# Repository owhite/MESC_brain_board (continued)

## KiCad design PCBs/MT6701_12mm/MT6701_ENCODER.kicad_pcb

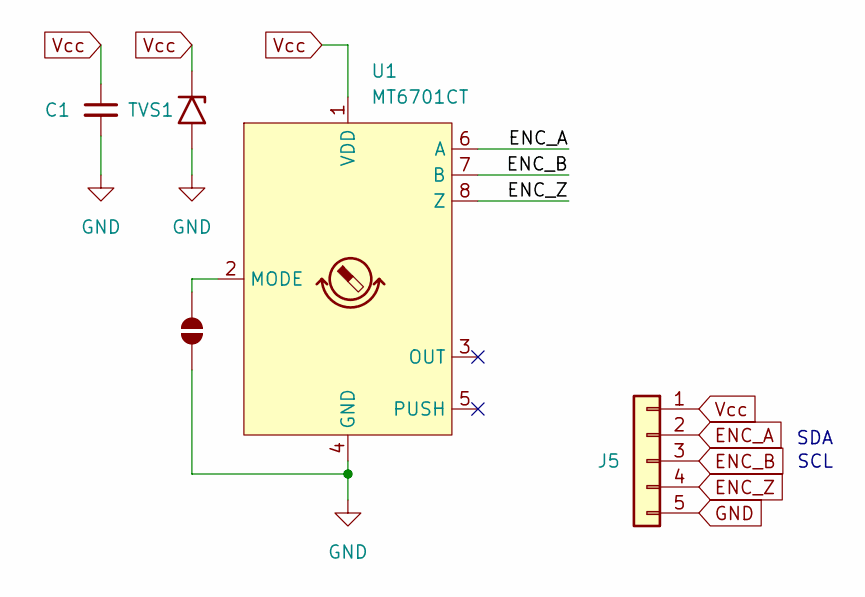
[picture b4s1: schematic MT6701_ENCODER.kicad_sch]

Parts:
C1: C_Small; C_0603_1608Metric
J5: Conn_01x05; PinSocket_1x05_P2.54mm_Vertical
JP1: SolderJumper_2_Open; SolderJumper-2_P1.3mm_Open_RoundedPad1.0x1.5mm
TVS1: SMFJ6.0A / SMFJ6.0CA; C_0805_2012Metric
U1: MT6701CT; SO-8_3.9x4.9mm_P1.27mm

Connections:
ENC_A: J5.2, U1.6 (A)
ENC_B: J5.3, U1.7 (B)
ENC_Z: J5.4, U1.8 (Z)
GND: C1.2, J5.5, JP1.2 (B), TVS1.2 (A2), U1.4 (GND)
unnamed: JP1.1 (A), U1.2 (MODE)
Vcc: C1.1, J5.1, TVS1.1 (A1), U1.1 (VDD)

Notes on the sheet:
SDA
SCL

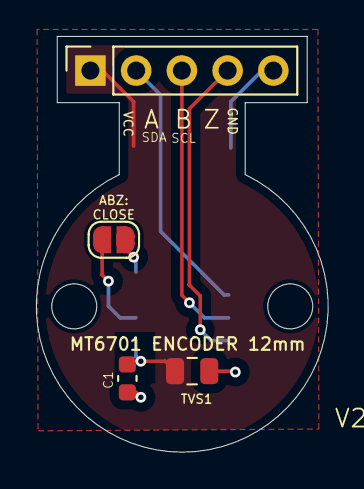
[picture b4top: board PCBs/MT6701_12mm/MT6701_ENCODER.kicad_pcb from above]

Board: 2 copper layers, 16.2 x 23.1 mm, 5 parts (1 on the bottom side), 6 nets.

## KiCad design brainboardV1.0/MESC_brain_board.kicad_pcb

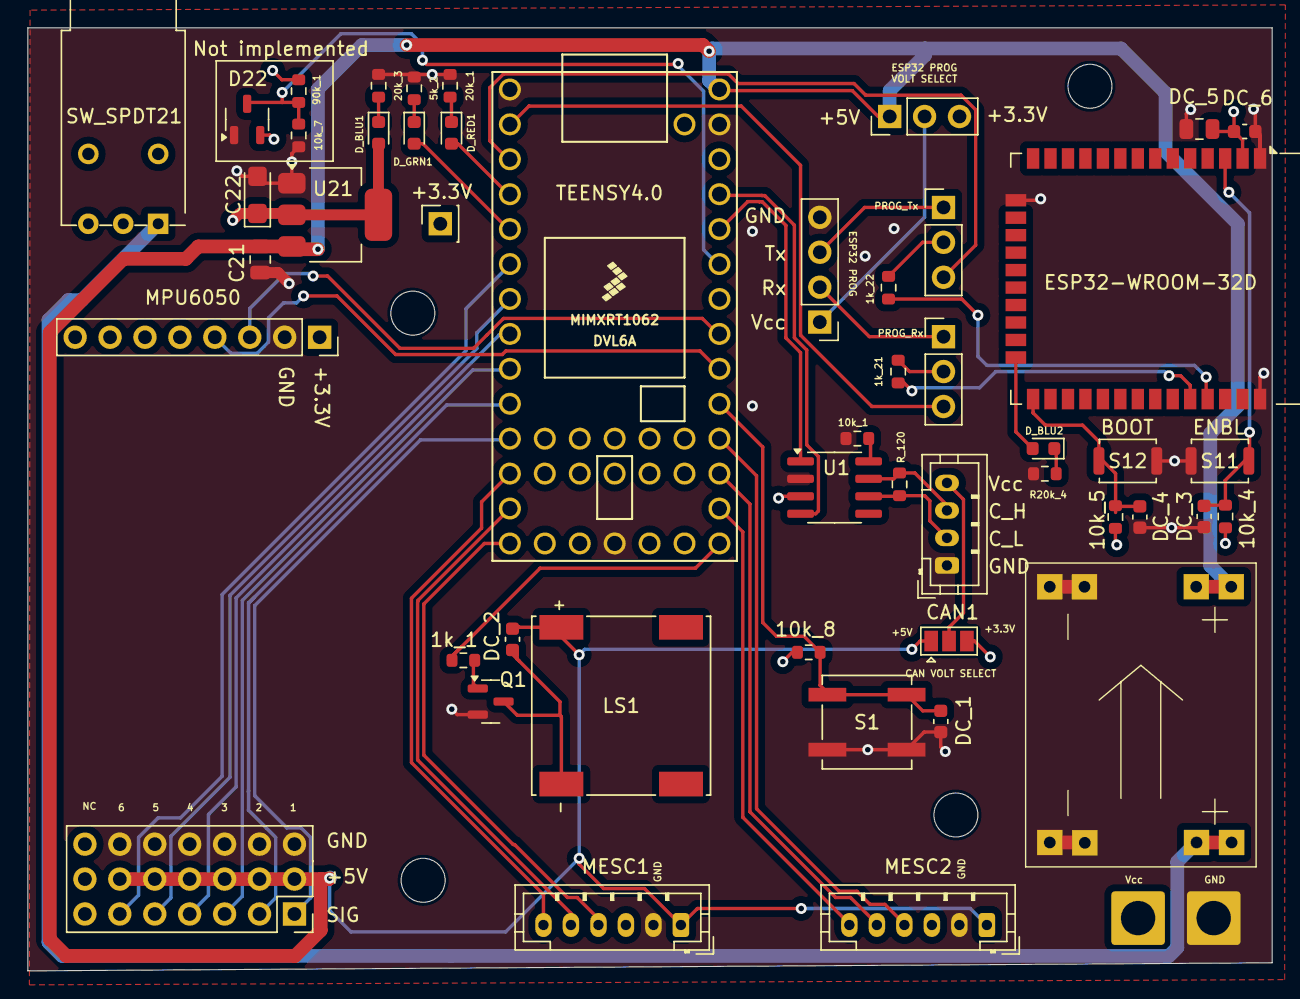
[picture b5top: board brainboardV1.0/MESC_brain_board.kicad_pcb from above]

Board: 4 copper layers, 90.5 x 68.6 mm, 51 parts (0 on the bottom side), 48 nets.

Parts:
1k_1, 10k_1, 10k_4, 10k_5, 10k_7, 10k_8: 10k; R_0603_1608Metric
1k_21, 1k_22: 1k; R_0603_1608Metric
5k_2: 5k; R_0603_1608Metric
20k_1, 20k_3: 20k; R_0603_1608Metric
90k_1: 90k; R_0603_1608Metric
C21: 10uF; C_0805_2012Metric
C22: C_Polarized_Small_US; CP_EIA-3216-18_Kemet-A
CAN1: Conn_01x04; JST_PH_B4B-PH-K_1x04_P2.00mm_Vertical
D22: BAT54S; SOT-23-3
DC_1, DC_2, DC_3, DC_4, DC_6: 100nF; C_0603_1608Metric
DC_5: 10uF; C_0805_2012Metric
D_BLU1: LED BLU; LED_0603_1608Metric
D_BLU2: BLUE; LED_0603_1608Metric
D_GRN1: LED GRN; LED_0603_1608Metric
D_RED1: LED RED; LED_0603_1608Metric
J1: Conn_01x18; my_PinSocket_3x07_P2.54mm_Vertical
J12, J13, J15: Conn_01x03; PinHeader_1x03_P2.54mm_Vertical
J14: SERIAL1; PinHeader_1x04_P2.54mm_Vertical
J22: Conn_01x01; PinSocket_1x01_P2.54mm_Vertical
J24, J25: Conn_01x01; SolderWire-2sqmm_1x01_D2mm_OD3.9mm
JP1: SolderJumper_3_Open; SolderJumper-3_P1.3mm_Open_Pad1.0x1.5mm
LS1: Speaker; SPKR_CDS-13138-SMT-TR
MESC1, MESC2: Conn_01x06; JST_PH_B6B-PH-K_1x06_P2.00mm_Vertical
MP1: Conn_01x08; PinSocket_1x08_P2.54mm_Vertical
Q1: my_BC337; SOT-23
R20k_4: 20k; R_0603_1608Metric
R_120: 120; R_0603_1608Metric
S1: TL3342F160QG; SW_SPST_B3SL-1022P
S11, S12: TL3342F160QG; SW_Push_SPST_NO_Alps_SKRK
SW_SPDT21: SW_SPDT; SW_NKK_BB15AH
U1: TJA1050T/CM,118; SOIC-8_3.9x4.9mm_P1.27mm
U2: Teensy4.0; Teensy40
U11: ESP32-WROOM-32D
U21: LD1117S18TR_SOT223; SOT-223-3_TabPin2
U22: my_buck_boost

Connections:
+3.3V: 10k_4.2, 10k_5.2, 10k_8.2, C22.1, D22.2, DC_5.2, DC_6.1, D_BLU1.2 (A), J15.3, J22.1, JP1.3 (B), MP1.1, U1.3 (VCC), U11.2 (VDD), U21.2 (VO)
+5V: C21.1, DC_2.1, J1.2, J1.5, J1.8, J1.11, J1.14, J1.17, J15.1, JP1.1 (A), LS1.1, MESC1.1, MESC2.1, U2.33 (VIN), U21.3 (VI), U22.7 (Reg_out), U22.8 (Reg_out)
/CAN_RX: U1.4 (R), U2.30 (23_A9_CRX1_MCLK1)
/CAN_TX: U1.1 (D), U2.29 (22_A8_CTX1)
/MPU6050_SCL: MP1.3, U2.26 (19_A5_SCL0)
/MPU6050_SDA: MP1.4, U2.25 (18_A4_SDA0)
BUTTON: 10k_8.1, DC_1.2, S1.2, U2.24 (17_A3_TX4_SDA1)
CAN_HI: CAN1.3, R_120.2, U1.7 (CANH)
CAN_LO: CAN1.2, R_120.1, U1.6 (CANL)
ESP_EN: 10k_4.1, DC_3.2, S11.2, U11.3 (EN)
ESP_RX: J12.3, U2.2 (0_RX1_CRX2_CS1)
ESP_RX_OUT: J12.1, J14.2
ESP_TX: J13.3, U2.3 (1_TX1_CTX2_MISO1)
ESP_TX_OUT: J13.1, J14.3
GND: 5k_2.1, 10k_1.2, 10k_7.2, 20k_1.1, 20k_3.1, C21.2, C22.2, CAN1.1, D22.1, DC_1.1, DC_3.1, DC_4.1, DC_5.1, DC_6.2, J1.3, J1.6, J1.9, J1.12, J1.15, J1.18, J14.4, J24.1, MESC1.2, MESC2.2, MP1.2, Q1.2 (E), R20k_4.1, S1.1, S11.1, S12.1, U1.2 (GND), U2.1 (GND), U2.17 (GND), U2.32 (GND), U11.1 (GND), U11.15 (GND), U11.38 (GND), U21.1 (GND), U22.1 (IN_-), U22.2 (IN_-), U22.5 (Reg_GND), U22.6 (Reg_GND)
IO0: 10k_5.1, DC_4.2, S12.2, U11.25 (IO0)
LED1: D_RED1.2 (A), U2.4 (2_OUT2)
LED2: D_GRN1.2 (A), U2.5 (3_LRCLK2)
unnamed: CAN1.4, JP1.2 (C)
unnamed: 20k_3.2, D_BLU1.1 (K)
unnamed: D_BLU2.2 (A), U11.24 (IO2)
unnamed: D_BLU2.1 (K), R20k_4.2
unnamed: 5k_2.2, D_GRN1.1 (K)
unnamed: 20k_1.2, D_RED1.1 (K)
unnamed: 1k_21.2, J12.2
unnamed: 1k_22.2, J13.2
unnamed: J14.1, J15.2
unnamed: 1k_1.1, Q1.1 (B)
unnamed: DC_2.2, LS1.2, Q1.3 (C)
unnamed: SW_SPDT21.1 (A), U22.3 (IN_+), U22.4 (IN_+)
unnamed: 10k_1.1, U1.8 (Rs)
PB3_1: MESC1.6, U2.12 (10_CS_MQSR)
PB3_2: MESC2.6, U2.21 (14_A0_TX3_SPDIF_OUT)
PB4_1: MESC1.5, U2.13 (11_MOSI_CTX1)
PB4_2: MESC2.5, U2.22 (15_A1_RX3_SPDIF_IN)
PB5_1: MESC1.4, U2.14 (12_MISO_MQSL)
PB5_2: MESC2.4, U2.23 (16_A2_RX4_SCL1)
RC_Mode: J1.7, U2.9 (7_RX2_OUT1A)
RC_Steering: J1.1, U2.11 (9_OUT1C)
RC_Throttle: J1.4, U2.10 (8_TX2_IN1)
RC_X: J1.10, U2.8 (6_OUT1D)
RC_Y: J1.13, U2.7 (5_IN2)
RC_Z: J1.16, U2.6 (4_BCLK2)
SPEAKER: 1k_1.2, U2.20 (13_SCK_CRX1_LED)
U0RXD: 1k_21.1, U11.34 (RXD0/IO3)
U0TXD: 1k_22.1, U11.35 (TXD0/IO1)
VSENSE: 10k_7.1, 90k_1.2, D22.3, U2.28 (21_A7_RX5_BCLK1)
Vcc: J25.1, SW_SPDT21.2 (B)

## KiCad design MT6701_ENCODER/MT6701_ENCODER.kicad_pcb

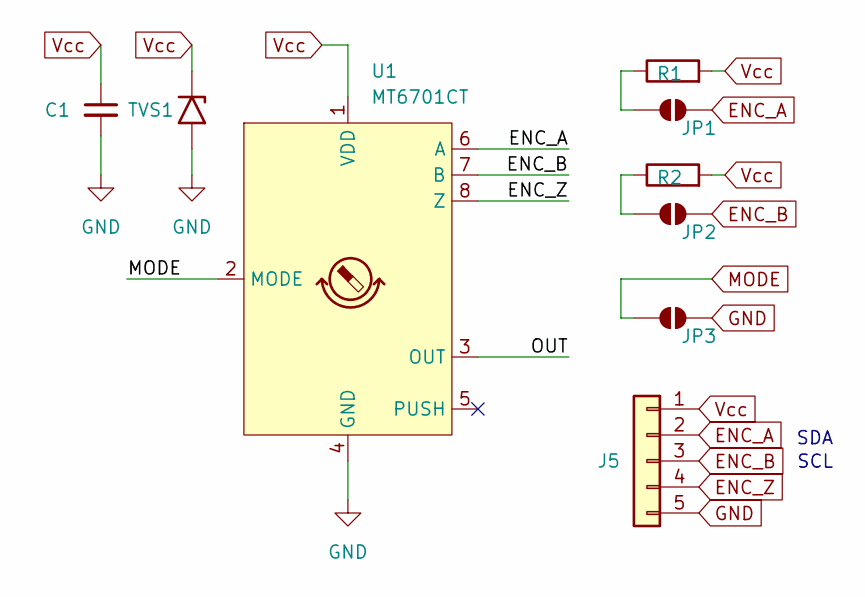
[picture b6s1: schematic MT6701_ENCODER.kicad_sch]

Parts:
C1: C_Small; C_0603_1608Metric
J5: Conn_01x05; PinHeader_1x05_P2.54mm_Vertical
JP1, JP2, JP3: SolderJumper_2_Open; SolderJumper-2_P1.3mm_Open_RoundedPad1.0x1.5mm
R1, R2: R; R_0603_1608Metric
TVS1: SMFJ6.0A / SMFJ6.0CA; C_0805_2012Metric
U1: MT6701CT; SO-8_3.9x4.9mm_P1.27mm

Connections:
/OUT: U1.3 (OUT)
ENC_A: J5.2, JP1.2 (B), U1.6 (A)
ENC_B: J5.3, JP2.2 (B), U1.7 (B)
ENC_Z: J5.4, U1.8 (Z)
GND: C1.2, J5.5, JP3.2 (B), TVS1.2 (A2), U1.4 (GND)
MODE: JP3.1 (A), U1.2 (MODE)
unnamed: JP1.1 (A), R1.1
unnamed: JP2.1 (A), R2.1
Vcc: C1.1, J5.1, R1.2, R2.2, TVS1.1 (A1), U1.1 (VDD)

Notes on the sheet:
SDA
SCL

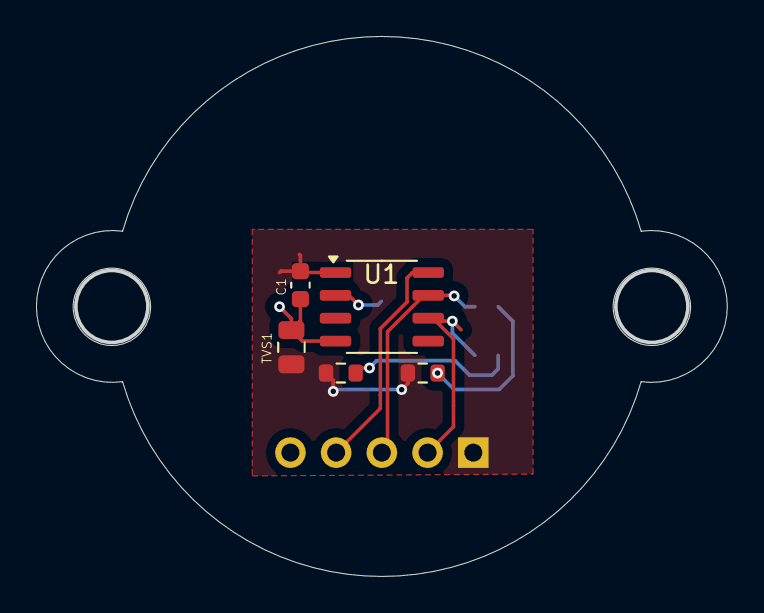
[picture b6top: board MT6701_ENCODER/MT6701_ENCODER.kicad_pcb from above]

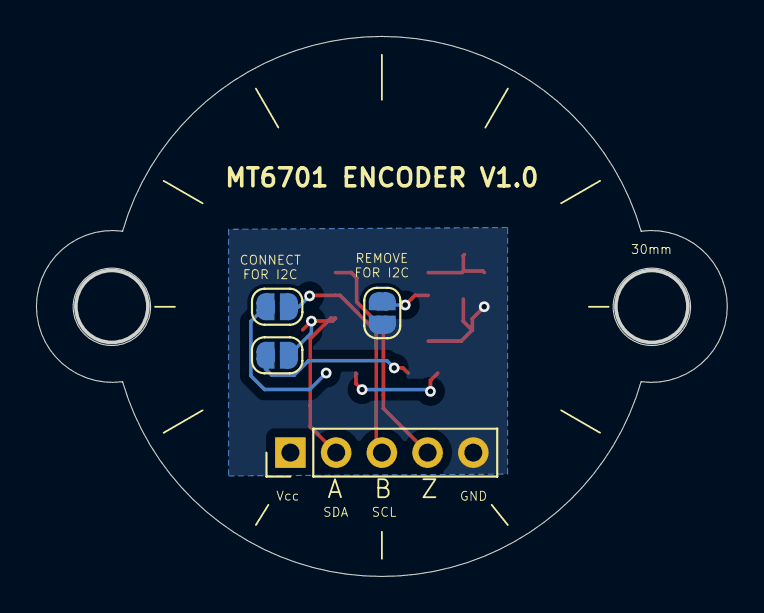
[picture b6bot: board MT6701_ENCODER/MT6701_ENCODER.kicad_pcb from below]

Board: 4 copper layers, 38.2 x 29.9 mm, 9 parts (4 on the bottom side), 8 nets.

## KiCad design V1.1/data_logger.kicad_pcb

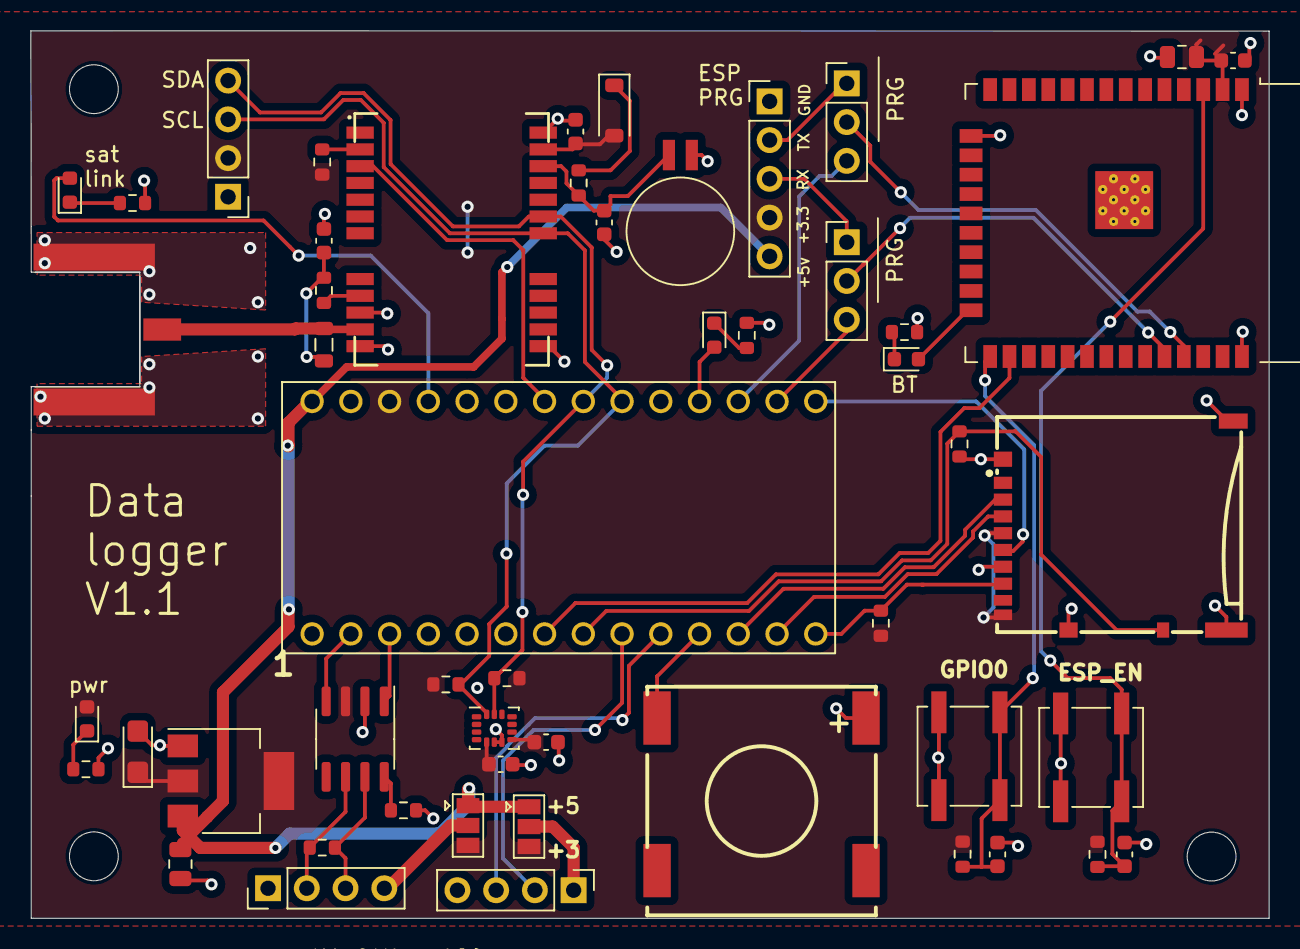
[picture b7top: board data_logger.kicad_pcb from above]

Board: 2 copper layers, 81.2 x 58.2 mm, 52 parts (0 on the bottom side), 43 nets.

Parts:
ANT1: U.FL; molex_ 0732519780
BT1: Battery_Cell; BatteryHolder_Seiko_MS621F
C1, C3: 1uF; C_0603_1608Metric
C2: 47pF; C_0603_1608Metric
C4, C8: 10uF; C_0805_2012Metric
C7, C11, C12, C13, C14: 100nF; C_0603_1608Metric
C10: C_Polarized_Small_US; CP_EIA-3216-18_Kemet-A
D1, D4: LED RED; LED_0603_1608Metric
D2: D_Schottky; D_SOD-123
D3: LED GRN; LED_0603_1608Metric
D5: LED BLU; LED_0603_1608Metric
J1: SERIAL1; PinHeader_1x04_P2.54mm_Vertical
J2: Conn_01x04; PinHeader_1x04_P2.54mm_Vertical
J3, J4: Conn_01x03; PinHeader_1x03_P2.54mm_Vertical
J5: Conn_01x05; PinHeader_1x05_P2.54mm_Vertical
J6: GPS1; PinHeader_1x04_P2.54mm_Vertical
J7: Micro_SD_Card; TF-SMD_TF-013-A
JP1, JP2: SolderJumper_3_Open; SolderJumper-3_P1.3mm_Open_Pad1.0x1.5mm
L1: 27nH; L_0805_2012Metric
LS1: Speaker; BUZ-SMD_5P-L15.0-W15.0-P13.7-BL
R1, R4, R12, R13, R15: 20k; R_0603_1608Metric
R2, R7, R8, R9, R10, R11, R14: 10k; R_0603_1608Metric
R3: 1k; R_0603_1608Metric
R5: 120; R_0603_1608Metric
R6: 10; R_0603_1608Metric
S1, S2: TL3342F160QG; SW_SPST_B3SL-1022P
U1: TJA1050T/CM,118; SOIC-8_3.9x4.9mm_P1.27mm
U2: LSM6DS3; LGA-14_3x2.5mm_P0.5mm_LayoutBorder3x4y
U3: NEO-M9N
U4: LD1117S18TR_SOT223; SOT-223-3_TabPin2
U6: DEV-15583; MODULE_DEV-15583
U7: ESP32-WROOM-32D

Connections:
+3.3V: C3.2, C7.1, C8.2, C10.1, C11.1, C14.1, D2.2 (A), D4.2 (A), J5.4, J6.2, J7.4 (VDD), J7.9 (SW1), JP1.3 (B), JP2.3 (B), R7.2, R8.1, R9.1, R10.2, R11.2, R13.2, U1.3 (VCC), U2.5 (VDDIO), U2.8 (VDD), U3.23 (VCC), U4.2 (VO), U6.3.3V_2, U7.2 (VDD)
+5V: C4.1, J5.5, JP1.1 (A), JP2.1 (A), U4.3 (VI), U6.VIN
/RF: ANT1.3, L1.1, U3.11 (RF_IN)
BACKUP: BT1.1 (+), C1.2, R3.1, U3.22 (V_BCKP)
CAN_HI: J2.3, R5.2, U1.7 (CANH)
CAN_LO: J2.2, R5.1, U1.6 (CANL)
CAN_RX: U1.4 (R), U6.0
CAN_TX: U1.1 (D), U6.1
CLK: J7.5 (CLK), U6.13
CS: J7.2 (DAT3/CD), U6.10
ESP_EN: C12.2, R10.1, S1.2, U7.3 (EN)
ESP_IO: U6.5, U7.26 (IO4)
ESP_RX: J3.3, U6.14
ESP_RX_OUT: J3.1, J5.3
ESP_TX: J4.3, U6.15
ESP_TX_OUT: J4.1, J5.2
GND: ANT1.1, ANT1.2, BT1.2 (-), C1.1, C2.1, C3.1, C4.2, C7.2, C8.1, C10.2, C11.2, C12.1, C13.1, C14.2, J1.4, J2.1, J5.1, J6.1, J7.6 (VSS), J7.10 (GND), J7.12 (GND), J7.13 (GND), J7.14 (GND), LS1.1, R1.1, R2.2, R4.1, R12.1, R14.1, R15.1, S1.1, S2.1, U1.2 (GND), U2.6 (GND), U2.7 (GND), U3.10 (GND), U3.12 (GND), U3.13 (GND), U3.24 (GND), U4.1 (GND), U6.G1, U6.G3, U7.1 (GND), U7.15 (GND), U7.38 (GND), U7.39 (GND)
IO0: C13.2, R11.1, S2.2, U7.25 (IO0)
LED1: D1.2 (A), U6.23
LED2: D3.2 (A), U6.16
MISO: J7.7 (DAT0), R13.1, U6.12
MOSI: J7.3 (CMD), U6.11
unnamed: C2.2, L1.2, R6.2
unnamed: D1.1 (K), R1.2
unnamed: D2.1 (K), R3.2
unnamed: D3.1 (K), R4.2
unnamed: D4.1 (K), R15.2
unnamed: D5.2 (A), U7.24 (IO2)
unnamed: D5.1 (K), R12.2
unnamed: J1.1, JP1.2 (C)
unnamed: J2.4, JP2.2 (C)
unnamed: R2.1, U1.8 (Rs)
unnamed: R7.1, U3.2 (D_SEL)
unnamed: R6.1, U3.9 (VCC_RF)
PPS: U3.3 (TIMEPULSE), U6.20
RX2: J1.2, U6.7
SCL: J6.4, R9.2, U2.13 (SCL), U3.19 (SCL/SPI_CLK), U6.19
SDA: J6.3, R8.2, U2.14 (SDA), U3.18 (SDA/~SPI_CS), U6.18
SD_DET: J7.11 (SW2), R14.2, U6.6
SPK: LS1.2, U6.9
TX2: J1.3, U6.8
U0RXD: J3.2, U7.34 (RXD0/IO3)
U0TXD: J4.2, U7.35 (TXD0/IO1)

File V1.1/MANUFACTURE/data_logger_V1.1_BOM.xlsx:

Comment | Designator | Footprint | LCSC
1uF | C1,C3 | Capacitor_SMD:C_0603_1608Metric | C15849
C_Polarized_Small_US | C10 | Capacitor_Tantalum_SMD:CP_EIA-3216-18_Kemet-A | C7171
47pF | C2 | Capacitor_SMD:C_0603_1608Metric | C1671
10uF | C4,C8 | Capacitor_SMD:C_0805_2012Metric | C15850
100nF | C7,C11,C12,C13,C14 | Capacitor_SMD:C_0603_1608Metric | C14663
LED RED | D1 | LED_SMD:LED_0603_1608Metric | C2286
D_Schottky | D2 | Diode_SMD:D_SOD-123 | C8598
LED GRN | D3 | LED_SMD:LED_0603_1608Metric | C72043
LED BLU | D4,D5 | LED_SMD:LED_0603_1608Metric | C72041
Micro_SD_Card | J7 | Connector_Card:TF-SMD_TF-013-A | C444917
27nH | L1 | Inductor_SMD:L_0805_2012Metric | C1330812
Speaker | LS1 | Buzzer_Beeper:BUZ-SMD_5P-L15.0-W15.0-P13.7-BL | C482341
20k | R1,R4,R12,R13,R15 | Resistor_SMD:R_0603_1608Metric | C4184
10k | R2,R7,R8,R9,R10,R11,R14 | Resistor_SMD:R_0603_1608Metric | C25804
1k | R3 | Resistor_SMD:R_0603_1608Metric | C21190
120 | R5 | Resistor_SMD:R_0603_1608Metric | C17437
10 | R6 | Resistor_SMD:R_0603_1608Metric | C22859
TL3342F160QG | S1,S2 | Button_Switch_SMD:SW_SPST_B3SL-1022P | C318884
TJA1050T/CM,118 | U1 | Package_SO:SOIC-8_3.9x4.9mm_P1.27mm | C6952
LSM6DS3 | U2 | Package_LGA:LGA-14_3x2.5mm_P0.5mm_LayoutBorder3x4y | C967633
LD1117S18TR_SOT223 | U4 | Package_TO_SOT_SMD:SOT-223-3_TabPin2 | C2984862
ESP32-WROOM-32D | U7 | RF_Module:ESP32-WROOM-32D | C529578

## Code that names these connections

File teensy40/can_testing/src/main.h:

#ifndef MAIN_H
#define MAIN_H

#include <Arduino.h>
#include <IntervalTimer.h>
#include <FlexCAN_T4.h>

// ================= MESC CAN definitions =================
#define CAN_ID_IQREQ    0x001
#define TEENSY_NODE_ID  0x03 // sender (is this Teensy)

// ================= Peripherals =================
#define LED1_PIN        2
#define LED2_PIN        3
#define PUSHBUTTON_PIN  19
#define SPEAKER_PIN     14
#define CS_PIN          10
#define INT_PIN         20
#define CAN_STB         21   // Verify this pin drives the CAN2 transceiver standby on brain_board V1.6.
// FlexCAN_T4 setRX()/setTX() takes FLEXCAN_PINS enum, not literal GPIO numbers.
// For CAN1 on Teensy 4.0, DEF selects CAN1_RX=pin 23 and CAN1_TX=pin 22.
#define CAN1_PINSEL     DEF
// Set to 0 to fully disable CAN1 traffic during A/B tests (TX and RX on Teensy side).
#define CAN1_ENABLE     1
// For CAN2 on Teensy 4.0, DEF selects CAN2_RX=pin 0 and CAN2_TX=pin 1.
#define CAN2_PINSEL     DEF

// CAN reliability improvement:
// A/B switch for receive servicing path under dual-bus load.
// CAN RX strategy A/B switch:
// 0 = polling in loop() (legacy behavior)
// 1 = ISR callback + events() dispatch
#ifndef CAN_RX_USE_ISR
#define CAN_RX_USE_ISR 1
#endif

// Global compile-time safety gate for wheel command transmission.
// 0 = never send IQREQ torque frames from Teensy
// 1 = allow IQREQ torque TX (normal behavior)
#ifndef SEND_TORQUE
#define SEND_TORQUE 1
#endif

// ================= CAN TX routing =================
// Route each ESC node to exactly one physical CAN controller.
// This avoids writing every command on both buses.
#define CAN_TX_BUS_CAN1 1
#define CAN_TX_BUS_CAN2 2
#define CAN_TX_BUS_BOTH 3

// Current bench mapping:
// - node 11 uses CAN2
// - node 12 uses CAN1
#define ESC_NODE11_TX_BUS CAN_TX_BUS_CAN2
#define ESC_NODE12_TX_BUS CAN_TX_BUS_CAN1

static inline uint8_t can_tx_bus_for_node(uint8_t node_id) {
  if (node_id == 11u) return ESC_NODE11_TX_BUS;
  if (node_id == 12u) return ESC_NODE12_TX_BUS;
  return CAN_TX_BUS_BOTH;  // fallback for unknown nodes
}

// Short chirp used by balance mode when theta_tared crosses zero.
void balance_zero_cross_tweet(void);



// ================= RC PWM channels =================
#define RC_INPUT1       4
#define RC_INPUT2       5
#define RC_INPUT3       6
#define RC_INPUT4       7
#define RC_INPUT5       8
#define RC_INPUT6       9

#endif // MAIN_H

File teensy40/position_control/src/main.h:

#ifndef MAIN_H
#define MAIN_H

#include <Arduino.h>
#include <IntervalTimer.h>
#include <FlexCAN_T4.h>

// ================= MESC CAN definitions =================
#define CAN_ID_IQREQ    0x001
#define TEENSY_NODE_ID  0x03 // sender (is this Teensy)

// ================= Peripherals =================
#define LED1_PIN        2
#define LED2_PIN        3
#define PUSHBUTTON_PIN  19
#define SPEAKER_PIN     14
#define CS_PIN          10
#define INT_PIN         20
#define CAN_STB         9
#define CAN_TX          24
#define CAN_RX          25



// ================= RC PWM channels =================
#define RC_INPUT1       21
#define RC_INPUT2       8
#define RC_INPUT3       7
#define RC_INPUT4       6
#define RC_INPUT5       5
#define RC_INPUT6       4

// Non-blocking short beeper chirp (uses TonePlayer state machine)
void beeper_tweet();

#endif // MAIN_H

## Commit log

2023-07-13 layout
2023-07-14 more schematic work
2023-07-17 more layout
2023-07-24 finishing pcb layout
2023-07-24 finalized pcb
2023-07-24 finished design
2023-07-25 manufacturing files
2023-07-25 ORDERED FROM JLCPCB
2023-08-11 fixed mistakes in V1.0, added in all firmware code
2023-08-22 drew the schematic
2023-09-02 more firmware work
2023-09-02 fixed GPS latency
2023-10-08 final?
2023-10-12 fixed extraneous text in blob?
2025-08-03 global name changes for all files
2025-08-04 nother checkin
2025-08-05 finished V1.0
2025-08-06 finalized PCB, changed file names
2025-08-06 finalizing PCB
2025-08-06 First board ordered from JLCPCB
2025-08-07 added docs
2025-08-12 adding more hardware docs
2025-08-19 added MT6701 board
2025-08-19 used for jlcpcb
2025-08-19 minor fix
2025-08-20 started board testing
2025-08-20 update grn LED resistor
2025-08-22 added software_specs.md
2025-08-22 new code in brain board
2025-08-22 added documentation
2025-08-27 started brain board framework
2025-08-27 added CAN documentation
2025-08-29 Add telemetry checklist for balancing robot development
2025-08-30 Add serial transmission performance documentation
2026-02-01 more documentation in /modeling
2026-02-02 CAD work
2026-02-13 minor stuff
2026-02-14 balancing work and documentation
2026-02-15 Create LICENSE
2026-02-15 Add LICENSE file
2026-02-15 lots of documentation
2026-02-16 version 2 encoder board
2026-02-16 refined vibration_test
2026-02-17 codex tuning
2026-02-19 preliminary wifi telemetry
2026-02-24 created encoder_testing, telemtry chain over ESP32
2026-02-24 brain board V1.4
2026-02-25 finalization of BB V1.4
2026-03-02 encoder work
2026-03-02 updated brainboard v1.4
2026-03-03 can_testing
2026-03-07 more CAN debugging
2026-03-21 docs: add GitHub-visible YouTube demo link
2026-03-21 worked on position control
2026-03-23 positional control work
2026-03-30 reasonable balance control, has minor drift issues
2026-04-02 Add RC transmitter test control for TWR
2026-04-02 stable, upright behavior
2026-04-12 improved CAN operations
2026-04-16 added virtual axle to reduce arc/drift to one side
2026-04-17 pretty good balancing in TWR
2026-04-22 TWR -> ESP32/wifi_repeater -> connect_raw.py working
2026-04-23 TWR -> ESP32/wifi_repeater improved packet sending
2026-05-04 working on motor damping docs
2026-05-19 completed more modeling of GB36-2
2026-05-22 Fix ESC POSVEL scheduler wrap and retire IQREQ keepalive workaround
    Add wrap-safe CAN telemetry timebase for autonomous POSVEL scheduling.
    Preserve IQREQ-triggered POSVEL sync/nudge behavior, restore POSVEL payload to position radians + velocity rad/s, keep ESC diagnostic status frames available for CAN bench testing, and update can_pos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
2026-05-31 motor docs
2026-06-21 Implement full OTA upload-download cycle with listener, orchestrator, firmware logging, and docs
2026-06-24 check in
